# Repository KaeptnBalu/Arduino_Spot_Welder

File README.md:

# Arduino_Spot_Welder
There is a new Version of this project available: https://github.com/KaeptnBalu/Arduino_Spot_Welder_V2

An Arduino based Spot Welder for battery welding
http://www.instructables.com/id/DIY-Arduino-Battery-Spot-Welder/

This Spot Welder can be used to weld 18650 batteries. It needs a 7-12V power source (12V recommended) and uses a 12V car battery as welding current supply. Typically one 45Ah battery delivers enough current to get good welds with 0.15mm nickel strips. For thicker nickel strips maybe you will need bigger battery or two in paralell.

The Welder generates a double pulse, where the first one is 1/8 of the time of the second one. Pulse time of second pulse is adjustable by the potentiometer and displayed on the screen in mS so you can exactly adjust the time. Its adjustable from 1 ... 20 mS.

If you want to download the project click on "Download ZIP" on this page. Downloading single files sometimes seems to cause some files to be corrupted while downloading.

You can get parts to build your own Spot Welder or prebuilt kits at https://malectrics.eu/

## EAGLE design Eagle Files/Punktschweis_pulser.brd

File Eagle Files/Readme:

The spot welder is made of two boards which are stacked on top of each other.
One board contains all the logic and low power electronic components and the other one contains the Mosfets.

---------------------------------------------------------------------------------------------------------

Update (01.2017): Spot_welder_gerber.zip is now accepted by pcb way without problems

---------------------------------------------------------------------------------------------------------

The gerber files are made to be used at pcbway.com 
You can support me by registering through this link http://www.pcbway.com/setinvite.aspx?inviteid=12824
This way you get a 5$ coupon for your order and i get some credits at the shop which i can use for upcoming projects.

There are two versions of the gerber files available.

1.
You can use the Spot_welder_gerber.zip which has both boards combined to one big board. 
You have to cut this in half at home to get the two single boards.

2.
You can use the Arduino_Board_Gerber.zip and the Mosfet_Board_Gerber.zip . So you have one gerber file for each board. 
This means you have to order both boards seperately which is more expensive, but no cutting at home is required.
(these are not the latest Version at the moment, i will update them in some weeks.)

To download Zip files click on them and then click "view raw". 
Downloading by right click and "save as" does seem to cause problems.

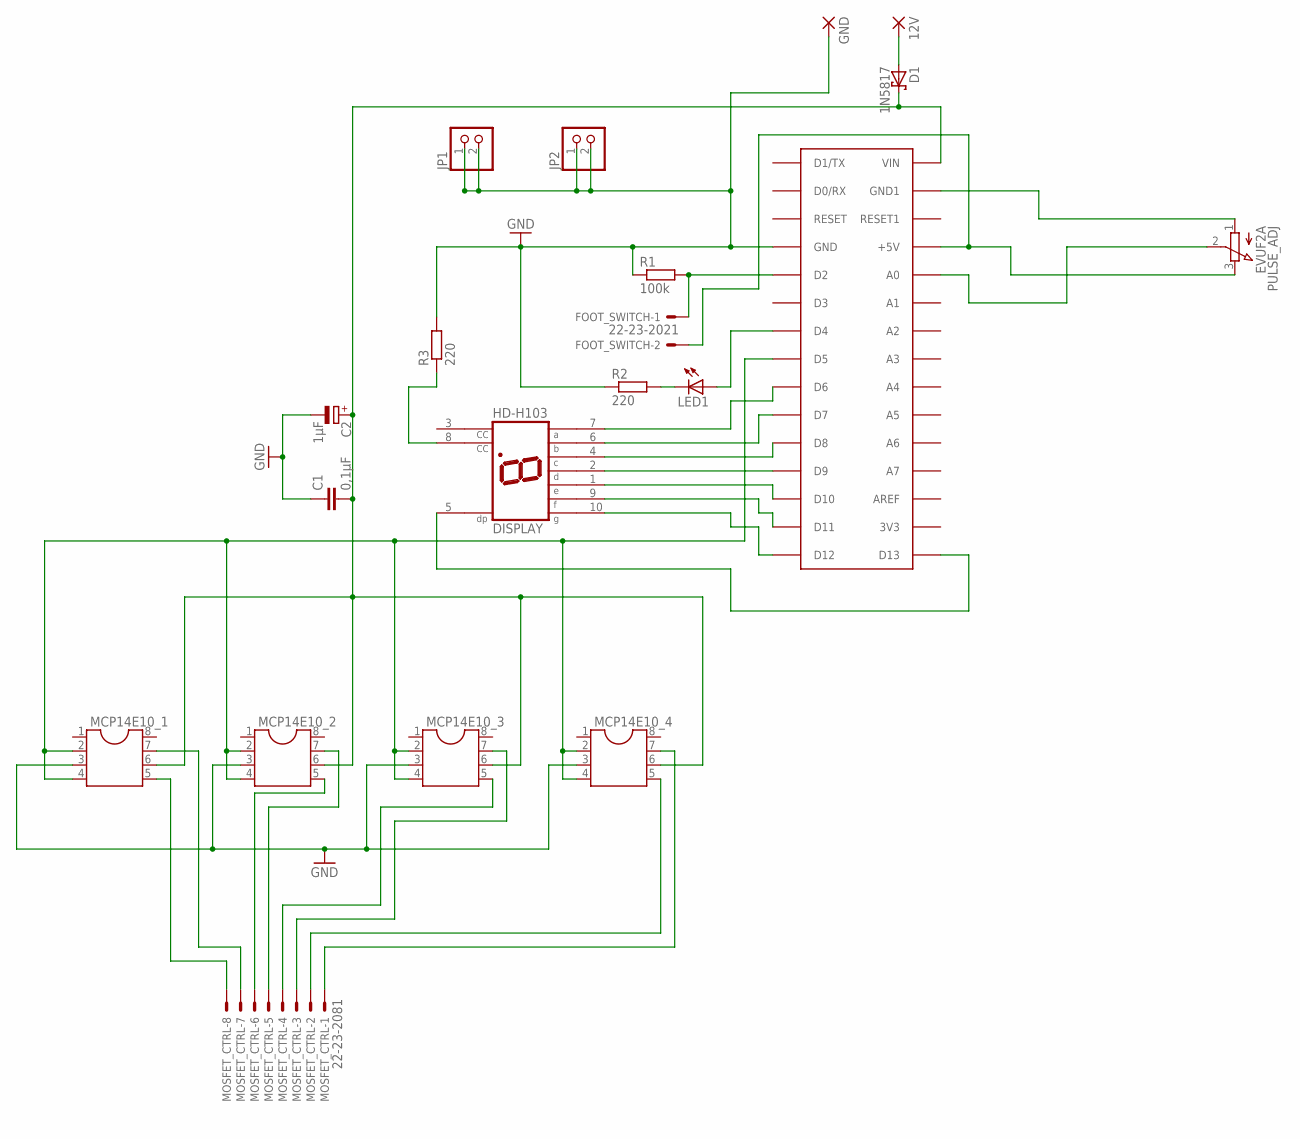
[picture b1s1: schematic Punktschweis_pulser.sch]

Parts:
12V: 2,54/0,8
C1: 0,1µF; C2.5-4
C2: 1µF; E2-5
D1: 1N5817; DO41-10
DISPLAY: HD-H103; HDSP-M
FOOT_SWITCH: 22-23-2021
GND: 2,54/0,8
JP1, JP2: PINHD-1X2; 1X02
LED1: LED5MM
MCP14E10_1, MCP14E10_2, MCP14E10_3, MCP14E10_4: DIL8; DIL08
MOSFET_CTRL: 22-23-2081
PULSE_ADJ: EVUF2A; EVUF
R1: 100k; 0207/10
R2, R3: 220; 0207/10
U$1: ARDUINONANO; PDIP-32

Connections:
GND: C1.1, C2.-, GND.1, JP1.1, JP1.2, JP2.1, JP2.2, MCP14E10_1.3, MCP14E10_2.3, MCP14E10_3.3, MCP14E10_4.3, R1.1, R2.1, R3.2, U$1.GND
unnamed: DISPLAY.7 (A), U$1.D6
unnamed: MCP14E10_1.5, MOSFET_CTRL.8
unnamed: C1.2, C2.+, D1.C, MCP14E10_1.6, MCP14E10_2.6, MCP14E10_3.6, MCP14E10_4.6, U$1.VIN
unnamed: PULSE_ADJ.1 (A), U$1.GND1
unnamed: FOOT_SWITCH.2, PULSE_ADJ.3 (E), U$1.+5V
unnamed: PULSE_ADJ.2 (S), U$1.A0
unnamed: FOOT_SWITCH.1, R1.2, U$1.D2
unnamed: LED1.K (C), R2.2
unnamed: LED1.A, U$1.D4
unnamed: MCP14E10_1.7, MOSFET_CTRL.7
unnamed: MCP14E10_2.5, MOSFET_CTRL.6
unnamed: MCP14E10_2.7, MOSFET_CTRL.5
unnamed: DISPLAY.6 (B), U$1.D7
unnamed: MCP14E10_3.5, MOSFET_CTRL.4
unnamed: MCP14E10_3.7, MOSFET_CTRL.3
unnamed: MCP14E10_4.5, MOSFET_CTRL.2
unnamed: MCP14E10_4.7, MOSFET_CTRL.1
unnamed: DISPLAY.4 (C), U$1.D8
unnamed: MCP14E10_1.2, MCP14E10_1.4, MCP14E10_2.2, MCP14E10_2.4, MCP14E10_3.2, MCP14E10_3.4, MCP14E10_4.2, MCP14E10_4.4, U$1.D5
unnamed: DISPLAY.2 (D), U$1.D9
unnamed: DISPLAY.1 (E), U$1.D10
unnamed: DISPLAY.9 (F), U$1.D11
unnamed: DISPLAY.10 (G), U$1.D12
unnamed: DISPLAY.5 (DP), U$1.D13
unnamed: DISPLAY.8 (CC), R3.1
unnamed: 12V.1, D1.A

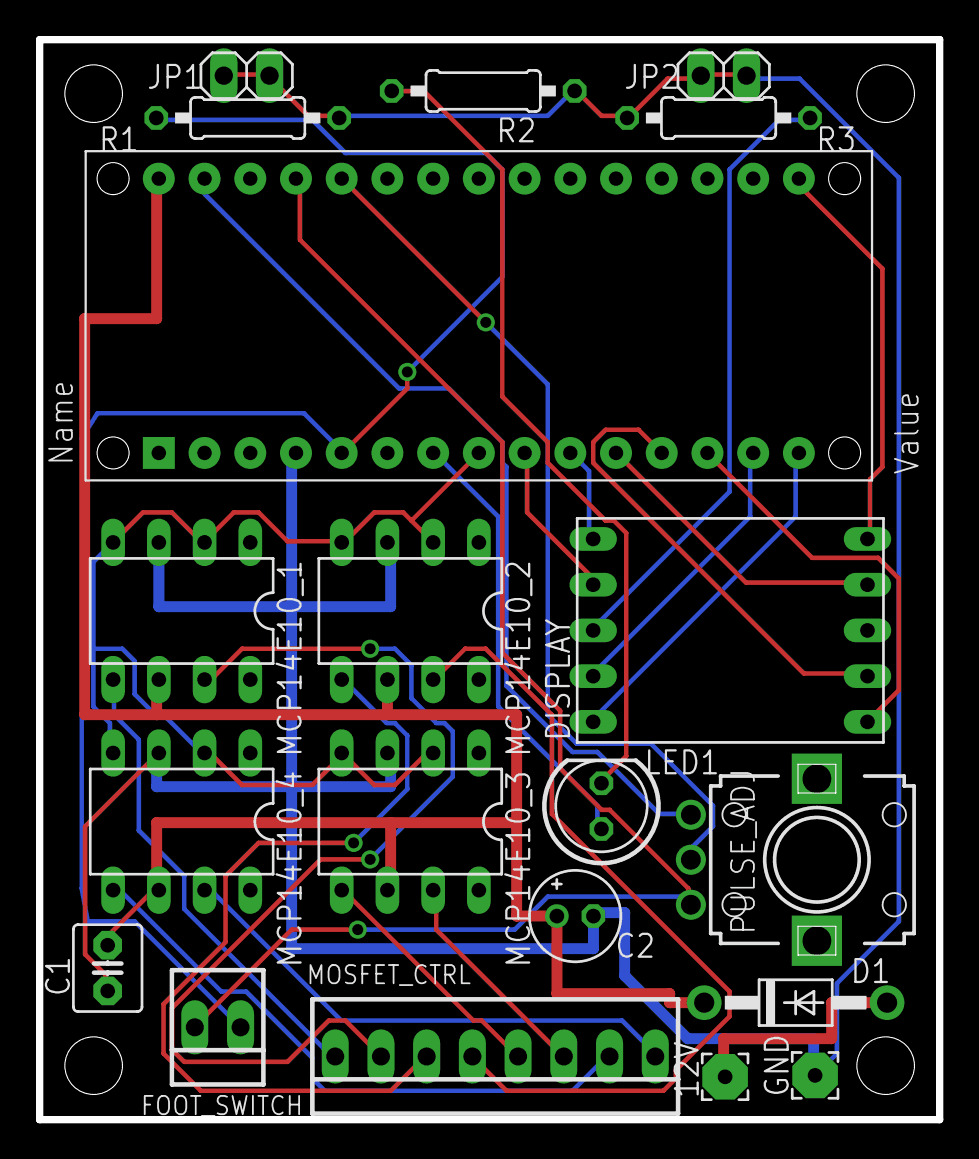
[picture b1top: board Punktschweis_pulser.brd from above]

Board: 2 copper layers, 50.0 x 60.0 mm, 20 parts (0 on the bottom side), 27 nets.

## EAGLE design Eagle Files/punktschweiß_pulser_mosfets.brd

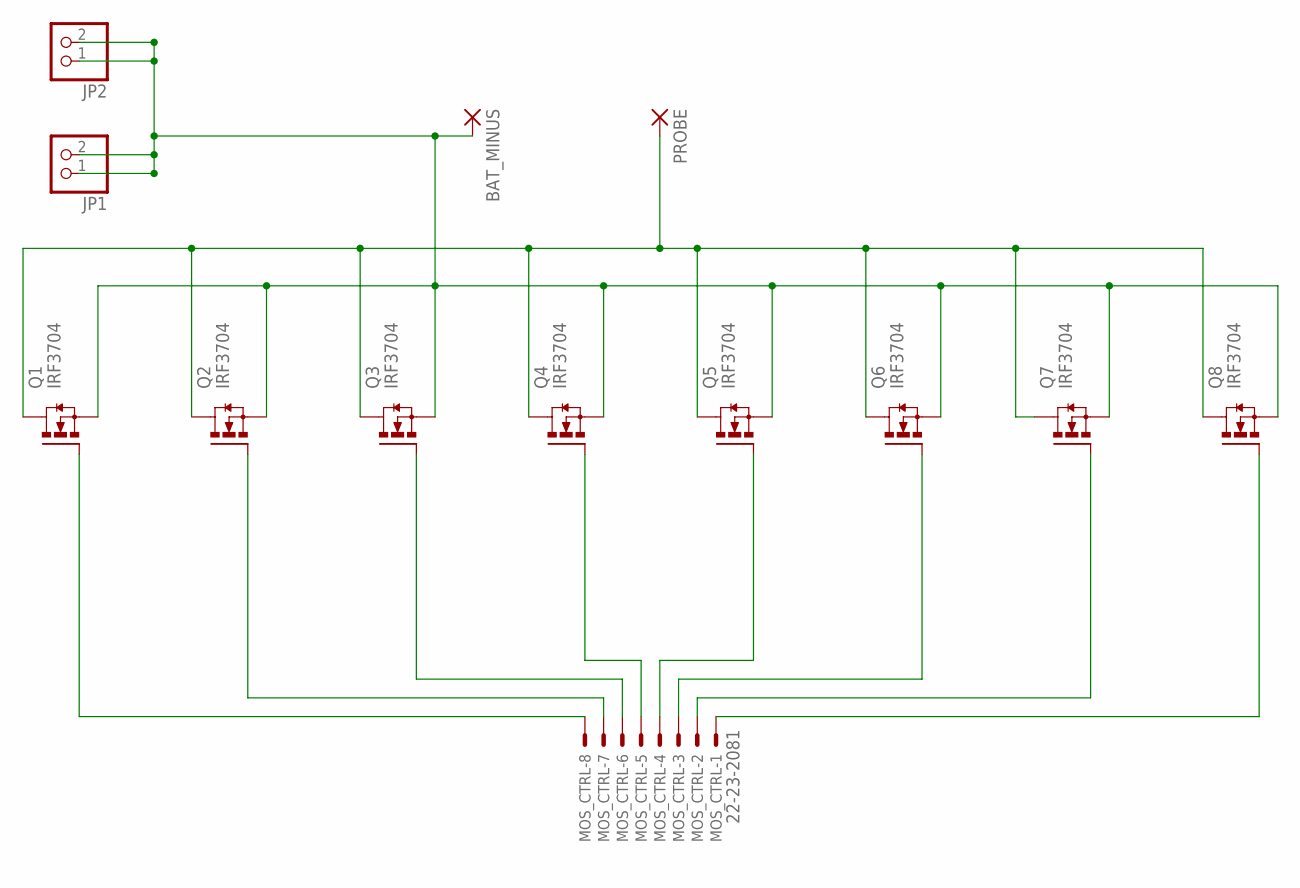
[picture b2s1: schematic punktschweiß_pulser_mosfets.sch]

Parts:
BAT_MINUS: 2,54/0,9
JP1, JP2: PINHD-1X2; 1X02
MOS_CTRL: 22-23-2081
PROBE: 2,54/0,9
Q1, Q2, Q3, Q4, Q5, Q6, Q7, Q8: IRF3704; TO220AH

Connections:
unnamed: MOS_CTRL.8, Q1.B (G)
unnamed: MOS_CTRL.7, Q2.B (G)
unnamed: MOS_CTRL.6, Q3.B (G)
unnamed: MOS_CTRL.5, Q4.B (G)
unnamed: MOS_CTRL.4, Q5.B (G)
unnamed: MOS_CTRL.3, Q6.B (G)
unnamed: MOS_CTRL.2, Q7.B (G)
unnamed: MOS_CTRL.1, Q8.B (G)
unnamed: BAT_MINUS.1, JP1.1, JP1.2, JP2.1, JP2.2, Q1.E (S), Q2.E (S), Q3.E (S), Q4.E (S), Q5.E (S), Q6.E (S), Q7.E (S), Q8.E (S)
unnamed: PROBE.1, Q1.C (D), Q2.C (D), Q3.C (D), Q4.C (D), Q5.C (D), Q6.C (D), Q7.C (D), Q8.C (D)

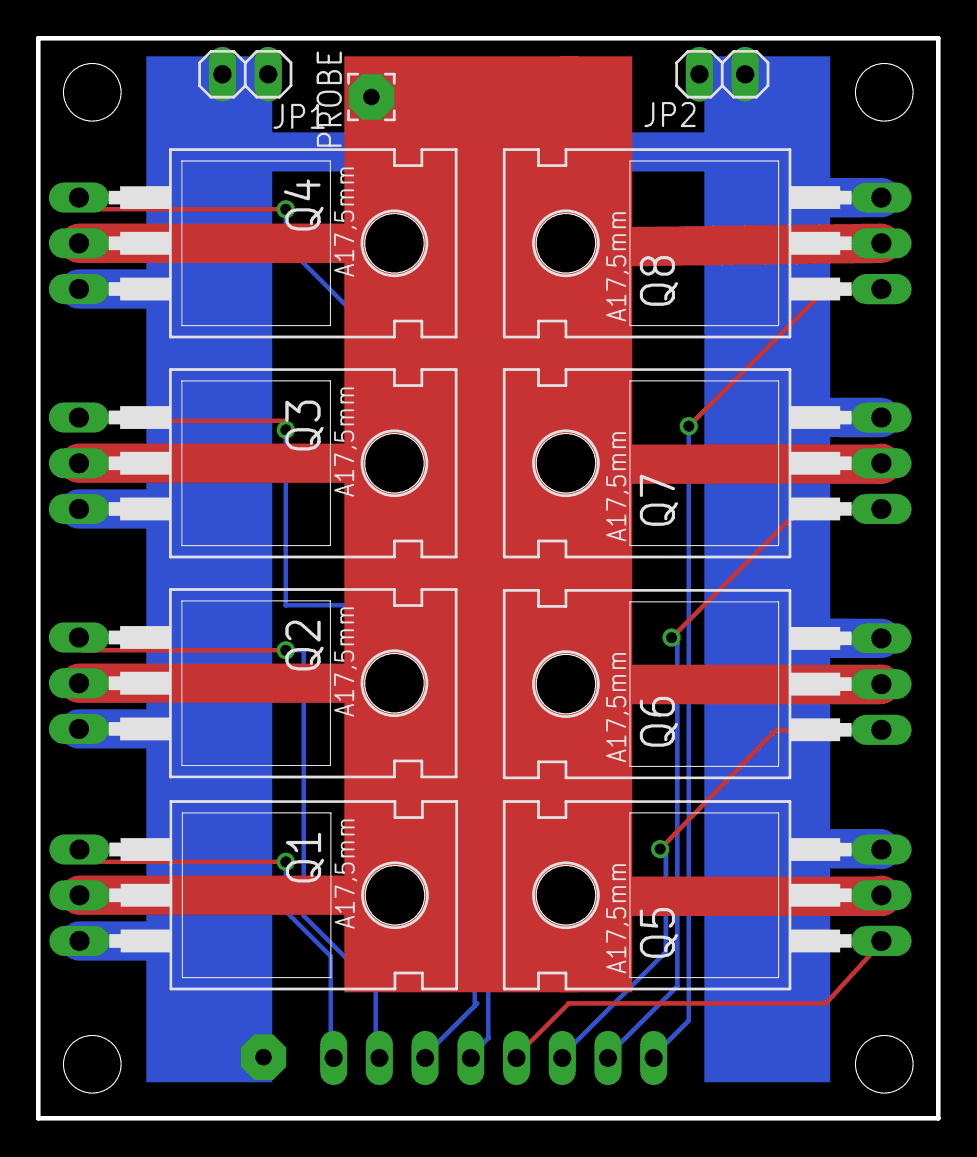
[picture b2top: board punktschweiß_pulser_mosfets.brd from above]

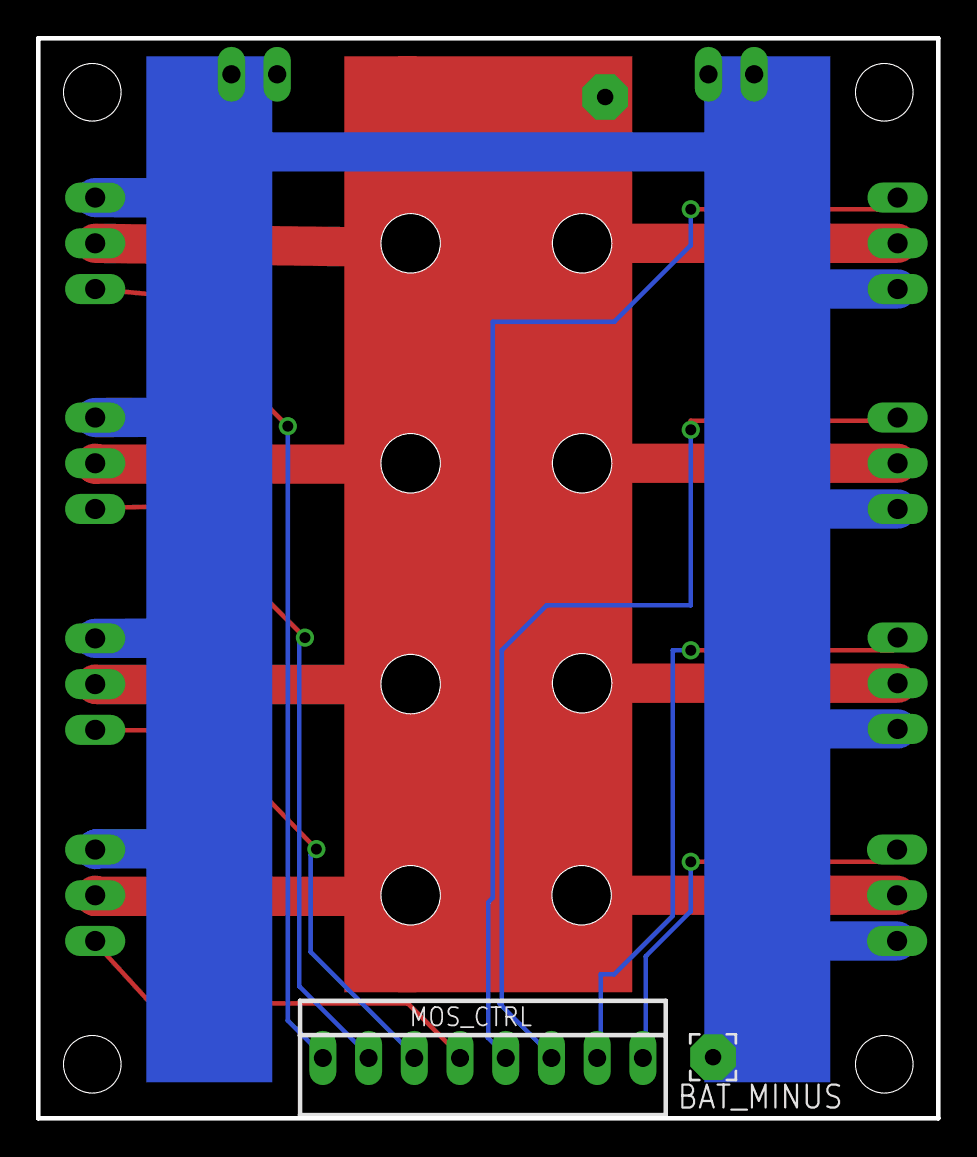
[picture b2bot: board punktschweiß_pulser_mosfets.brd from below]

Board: 2 copper layers, 50.0 x 60.0 mm, 13 parts (2 on the bottom side), 10 nets.

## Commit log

2016-01-30 Create Arduino Nano Code
2016-01-30 Arduino Nano Code
    the code run the spot welder
2016-01-30 Eagle files of the two boards
2016-01-30 assembly pictures
2016-01-30 parts to buy
2016-02-01 BOM update
2016-02-27 added pcb board to the BOM
2016-02-27 Arduino Code Readme
2016-02-27 added schematic and board pictures
2016-03-06 Added Gerber Files for pcbway.com
2016-03-08 some small improvements on the eagle files
2016-03-08 download instructions
2016-03-08 Gerber files description
2016-03-09 Make it Arduino friendly. just double click the .ino
2016-03-09 Add project desc, first test case
2016-03-09 fixed led
2016-03-09 small readme change
2016-03-17 Image of the Gerber File Board Layout
2016-03-17 some code improvement and comments added
2016-03-17 code improvements and comments added
2016-04-02 gerber board outlines fixed
2016-04-18 BOM updated
2016-05-10 Single boards gerber added
2016-06-12 Gerber improved
2016-06-13 removed dashed line from gerber
2016-09-03 Update Arduino sketch
    I have made lots of changes, but none to the features or operation of the spot welder. Mainly I have improved the display subroutine and the potentiometer reading.
    Most important changes:
    - Display code is now non-blocking. So pulse will happen as soon as switch is pressed, not a few hundred milliseconds later
    - Display updates immediately and shows ones place digit when adjusting pot
    - "1" digit in tens place shows on left which is more readable
    - Hysteresis added to the potentiometer reading
2016-09-03 Update Reichelt Part List
2016-12-08 Add files via upload
    little fixes on the silkscreen layer
2017-01-27 Add files via upload
    Some small improvements to the pcb layout
2017-01-30 3D and DXF drawing of the alu parts
2017-02-14 Code to find failures in the circuit
2017-02-14 Arduino Code Instructions
2017-03-01 Added max_pulse_time_variable
    With this variable right at the top of the code you can change the maximum pulse time to your demands.
